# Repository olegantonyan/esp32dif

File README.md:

# esp32dif

Wi-Fi to S/PDIF receiver. The PC sends audio over Wi-Fi, and an ESP32-C5-DevKitC-1 plays it on a PiFi Digi+ (WM8804) S/PDIF board.

- Lossless 16/24-bit PCM, 32–192 kHz, bit-perfect when PipeWire does not change the audio.
- Web UI, telnet and USB shell for setup and diagnostics.
- Firmware updates over Wi-Fi (OTA) with automatic rollback.
- Status and track title on two small OLED screens.

Firmware: ESP-IDF 6.1. Technical details: [docs/internals.md](docs/internals.md). Digi+ bring-up notes: [docs/digi-bringup.md](docs/digi-bringup.md).

## Build and flash

```sh
make build
make flash-monitor   # first time, over USB; TTY_PORT=/dev/ttyACM0 by default
make ota             # later, over Wi-Fi; ESP_HOST=esp32dif.local, ESP_PASSWORD=esp32dif-admin by default
```

Use the board's **USB** port (`/dev/ttyACM0`), not **UART** (`/dev/ttyUSB0` has no console).

Build settings are in `sdkconfig.defaults`. To create `sdkconfig` again: `rm sdkconfig && idf.py set-target esp32c5`.

## First setup

1. Flash the board over USB.
2. With no saved Wi-Fi, the board starts its own Wi-Fi network (access point) `esp32dif`. The password is on the OLED (default `esp32dif-admin`).
3. Join it from a phone or PC and open `http://192.168.4.1`. Log in as `admin` with the same password.
4. Pick your Wi-Fi network and press **Connect**. The board saves it after it gets an IP address.
5. Open `http://esp32dif.local` from your home network. The board's access point turns off 2 minutes after the connection works.

On the USB shell you can do the same with `wifi connect <ssid> <password>`.

## Access and settings

One password protects the web UI, telnet, the board's access point and audio senders. The USB shell has no password.

| Way | How |
|---|---|
| Web UI | `http://esp32dif.local` (or `http://192.168.4.1` on the access point), user `admin`. Status (with the current player and track), Wi-Fi, hostname, password, firmware upload, reboot. |
| Telnet | `telnet esp32dif.local`. Same commands as USB, one session at a time, logout after 10 minutes without input. |
| USB | `make monitor` |

Change the hostname and password in the web UI, or with `config hostname <name>` and `config password <pw>`. The board saves them and uses them at once. The back OLED shows the current password (128x64 always, 128x32 while the access point runs without Wi-Fi; if it's asleep, press a remote key or reboot), and `config password` works over USB, so you can't lock yourself out.

The password travels as plain text over HTTP and telnet. This is fine on a home network, but not on networks you don't trust.

## Wi-Fi

- The board connects to the saved network at every boot. If the connection drops, it tries again: 3 times at once, then after 5, 10, 20 and 40 s, then every 60 s.
- Band `auto` (default) prefers 5 GHz. Use `wifi connect -b 5` or `-b 2.4` to force a band.
- Power save is off, for low latency.
- The board gets its IP address from DHCP and answers as `<hostname>.local` (mDNS).
- **Access point:** the board starts its own network (named after the hostname, WPA2, the device password, `192.168.4.1`) when no network is saved, after `wifi disconnect`, or after 60 s without an IP address. It turns off 2 minutes after the home connection works again.

## Firmware updates (OTA)

`make ota`, or upload `build/esp32dif.bin` in the web UI. The board has two firmware slots. A new firmware is confirmed 60 s after it starts. If the board resets before that, it starts the old firmware again. `ota status` shows both slots; `ota rollback` goes back to the old firmware.

The first flash with this partition layout must be over USB (`make flash`). The saved Wi-Fi is kept.

If you rename the project, flash over USB too: OTA accepts only firmware with the same project name.

## Playing audio from the PC

The PC runs the `esp32dif-sink` service. It adds an output device "S/PDIF over Wi-Fi" to PipeWire. Select it in the sound settings, or play a file with `pw-play --target=esp32dif-rtp file.wav`.

### Install

Install the `esp32dif-sink` package from [repositories.omnipackage.org/esp32dif](https://repositories.omnipackage.org/esp32dif/install.html) (openSUSE, Fedora, Debian, Ubuntu, Arch, Manjaro). It is built from every master push that changes the sink. Then start the service:

```sh
systemctl --user daemon-reload && systemctl --user enable --now esp32dif-sink
journalctl --user -u esp32dif-sink -f
```

To turn it off for your user: `systemctl --user mask esp32dif-sink`.

- **Password:** every 10 s the service logs in to the board with `SPDIF_PASSWORD` (default `esp32dif-admin`). The board plays audio only from computers that logged in during the last 60 s. With a wrong password, the service logs an error and doesn't create the device.
- **Board offline:** the device disappears about 30 s after the board stops answering, and comes back about 10 s after the board returns. If the board's IP address changes, the service follows it.
- **Remote buttons:** the service also connects to the board on TCP 5005 and turns IR remote buttons, the board's `player` command and the web UI's Player buttons into media player commands with `playerctl`: previous, play/pause, next. They go to the player you used last. Volume up/down and mute change the volume of this PC's `esp32dif-rtp` device with `pactl` (steps of `SPDIF_VOLUME_STEP` %, up to 100 %); the audio stays bit-perfect only at 100 %. With two PCs connected, only the one streaming to the board gets them. Known remotes: Edifier S2000MKII (`ir keys`). Turn it off with `SPDIF_REMOTE=0`.
- **Track title:** over the same connection the service sends the artist, title, name and playback status of that player when any of them changes. While this PC is the board's last RTP source and the service stays connected, the front OLED shows the artist, the title and a play/pause/stop icon with the player name and id in a double-height font; long ones scroll. Between them it shows the device volume (`vol 45%` or `vol muted`), however you change it. Latin, accented Latin and Cyrillic letters are shown; other characters show as `?`.
- **Firewall:** allow mDNS on the PC (`firewall-cmd --permanent --zone=public --add-service=mdns`, then `firewall-cmd --reload`). Without it, `esp32dif.local` doesn't work; use the IP address instead.

### Settings

Settings go in `~/.config/esp32dif-sink.conf`, for example:

```sh
SPDIF_HOST=esp32dif.local
SPDIF_RATE=44100
SPDIF_FORMAT=S24BE
SPDIF_PASSWORD=esp32dif-admin
```

Run `chmod 600` on this file, because it has the password. Apply changes with `systemctl --user restart esp32dif-sink`. When you change the board's hostname or password, change them here too.

Other settings: `SPDIF_PORT` (5004), `SPDIF_SAP_PORT` (9875), `SPDIF_CHECK_S` (10), `SPDIF_MISSES` (3), `SPDIF_REMOTE` (1), `SPDIF_REMOTE_PORT` (5005), `SPDIF_VOLUME_STEP` (5).

### Without the package

If there is no package for your distro, link the files from this folder. The script needs `bash`, `pipewire`, `curl`, `playerctl`, `pactl` (`pulseaudio-utils`, `libpulse` on Arch) and `nss-mdns`.

```sh
ln -s "$PWD/pipewire/esp32dif-sink" ~/.local/bin/esp32dif-sink
systemctl --user link "$PWD/pipewire/esp32dif-sink.service"
systemctl --user enable --now esp32dif-sink
```

Or run it in a terminal:

```sh
pipewire/esp32dif-sink                              # esp32dif.local, 48000 Hz, S24BE
pipewire/esp32dif-sink esp32dif.local 44100 S24BE   # host, rate, format
```

### Sound quality

For bit-perfect output:
- set the device volume to 100 %,
- play nothing else at the same time,
- use the same rate in the file, the sink and the PipeWire graph. The default PipeWire graph runs only at 48 kHz. Add `default.clock.allowed-rates = [ 44100 48000 ]` to allow 44.1 kHz too, then set `SPDIF_RATE=44100`.

Measured with `digi decode -d` (24-bit noise and −3 dBFS sines, compared with the file):

| Path | Result |
|---|---|
| 48 kHz file → 48 kHz sink, 100 % volume | bit-perfect (269/269 frames) |
| same at 90 % volume | 0 frames exact |
| 44.1 kHz file → 44.1 kHz graph and sink | bit-perfect (270/270 frames) |
| 44.1 kHz → 48 kHz (resampled), 997 Hz / 15 kHz | SINAD 138.1 / 138.8 dB, error −144 dBFS |
| 48 kHz → 44.1 kHz (resampled), 15 kHz | SINAD 139.6 dB |
| native, 997 Hz (24-bit limit) | SINAD 143 dB |

How it works:
- The board plays a stream only when it has a matching SAP announcement (L16 or L24 stereo). It switches the WM8804 to the announced rate.
- The buffer adds 250 ms of latency. Video players don't know about it, so video and sound can be out of sync. The buffer is in PSRAM (1152 KB, 4 s at 48 kHz 24-bit), or 64 KB of internal RAM without PSRAM.
- The board slowly adjusts its clock to the PC's clock, so the buffer never runs empty or full. This doesn't change the audio data.
- `rtp status` shows senders, format, lost packets, jitter, buffer level, underruns and clock adjustment.

## Wiring

### Pins

| Function | GPIO | Header |
|---|---|---|
| RGB LED (WS2812) | 27 | J3 pin 7 |
| OLED and Digi+ I2C SDA / SCL | 8 / 9 | J1 pin 9 / 10 |
| Digi+ I2S BCLK / WS / DOUT | 24 / 23 / 4 | J3 pin 4 / 5 / 8 |
| S/PDIF monitor (optional, for `digi spdif`) | 5 | J3 pin 9 |
| IR receiver output (Digi+ HAT or any 38 kHz receiver, 3.3 V) | 10 | J1 pin 11 |
| BOOT button | 28 | J3 pin 11 |
| USB D- / D+ | 13 / 14 | J3 pin 14 / 13 |
| UART0 TX / RX | 11 / 12 | J3 pin 2 / 3 |

Don't use for new wiring: strapping pins 2, 3, 7, 25, 26, 27, 28; flash/PSRAM pins 16–22 (and 15 on PSRAM modules); 0 and 1 if a 32 kHz crystal is fitted.

Pins and I2C addresses can be changed in `idf.py menuconfig` (Board OLED, Board I2C bus, Board Digi+, Board LED, Board IR receiver).

### OLED

Two SSD1306 I2C modules on the same bus: **back** 0.91" 128x32 at 0x3C (status), **front** 0.96" 128x64 at 0x3D (track). Both are wired in parallel to header **J1** (the header with `3V3` at pin 1, see the [DevKitC-1 user guide](https://docs.espressif.com/projects/esp-dev-kits/en/latest/esp32c5/esp32-c5-devkitc-1/user_guide.html)):

| OLED pin | DevKitC-1 pin | Label on board |
|---|---|---|
| GND | J1 pin 15 | `G` |
| VCC | J1 pin 1 | `3V3` |
| SCL | J1 pin 10 | `9` |
| SDA | J1 pin 9 | `8` |

- Use 3V3, not 5V. With 5V the module's pull-ups would pull SDA/SCL to 5 V.
- 0.91" 128x32 modules are fixed at 0x3C (the panel has no address pin). Most 0.96" 128x64 modules have an address resistor on the back; move it to get 0x3D. `i2cscan` shows which addresses answer.
- Addresses, heights and 180° rotation of both displays can be changed in menuconfig (Board OLED).
- The board also works with one display or none.

### Digi+ (WM8804 S/PDIF HAT)

PiFi Digi+ 1.0, a HiFiBerry Digi+ clone. HAT pins are the physical pins of its 40-pin Raspberry Pi header.

| HAT pin | DevKitC-1 pin | Label on board | Signal |
|---|---|---|---|
| 2 | J1 pin 14 | `5V` | 5 V (the HAT makes its own 3.3 V) |
| 6 | J1 pin 15 | `G` | ground |
| 3 | J1 pin 9 | `8` | I2C SDA, shared with the OLEDs |
| 5 | J1 pin 10 | `9` | I2C SCL, shared with the OLEDs |
| 12 | J3 pin 4 | `24` | I2S BCLK, HAT → ESP |
| 35 | J3 pin 5 | `23` | I2S WS (LRCLK), HAT → ESP |
| 40 | J3 pin 8 | `4` | I2S DOUT, ESP → HAT |
| 39 | J3 pin 1 | `G` | ground, next to the I2S wires |
| 22 | J3 pin 9 | `5` | S/PDIF monitor (optional, for `digi spdif`), HAT → ESP |

- **Add 2.2 kΩ pull-ups** from SDA and SCL to 3V3. Without them, I2C fails while audio plays.
- Leave HAT pin 1 (3V3) open: the HAT makes its own 3.3 V from 5V.
- HAT pin 22 (BCM GPIO25) is unused by the HAT. For the S/PDIF monitor, solder a wire on the HAT from the optical transmitter's data pin to pin 22. Don't add a series resistor: the HAT's 200 Ω before the transmitter already protects TX0, and an extra 1 kΩ caused decode errors.
- Run `digi probe` to check the wiring step by step. More notes: [docs/internals.md](docs/internals.md#digi-wiring-notes).

## OLED screens

Back:

```
48kHz 24-bit         format
rtp 102ms buf        source: rtp, tone, idle; noI2C = no I2C to the WM8804
192.168.0.21         IP address or Wi-Fi state; on 128x32 the password while the access point is on without Wi-Fi
AP:- up 0d 01:02:03  access point clients (- = off), uptime
esp32dif.local       128x64 only: hostname
pw esp32dif-admin    128x64 only: password (first 18 characters)
heap 312 KB free     128x64 only: free memory
```

Front, while a PC sends the track title (see [Install](#install)), otherwise `no track`. Double-height font, 10 characters per line; longer text scrolls:

```
Pink Floyd           artist
Shine On Y           title
                     
▶ mpz (org           playback status icon, player and id
```

To prevent burn-in, each screen turns off after 2 minutes without activity. A remote key, a format or source change, a Wi-Fi or access point change, or any `oled` command wakes it. Change the timeout with `oled idle` or in menuconfig (Board OLED).

## Shell commands

The same commands work on USB and telnet. Line editing, history, Tab completion and `help [cmd]` are available.

| Command | What it does |
|---|---|
| `config show [-p]` | hostname, password (hidden without `-p`), access point |
| `config hostname <name>` | set hostname: a-z, 0-9, `-`, up to 32 characters |
| `config password <pw>` | set password: 8–63 characters |
| `wifi scan` | list nearby networks |
| `wifi connect [ssid] [password] [-b 2.4\|5\|auto] [-n] [-t s]` | join a network; it is saved after it gets an IP (`-n`: don't save). Without ssid: the saved network |
| `wifi status` | connection, signal, IP address, access point |
| `wifi saved [-p]` / `forget` / `disconnect` | show / delete the saved network / disconnect |
| `rtp status` / `rtp reset` | audio receiver statistics / reset them |
| `ota status` / `ota rollback` | firmware slots / go back to the old firmware |
| `digi status` | WM8804 found, crystal, rate, pins, tone |
| `digi probe` | check the Digi+ wiring step by step |
| `digi rate <hz>` | 32000, 44100 (default), 48000, 88200, 96000, 176400, 192000 |
| `digi tone <hz> [-l 0-100]` / `digi stop` | play a test sine (level in %, default 10) / stop it |
| `digi reg <reg> [value]` | read or write a WM8804 register |
| `digi spdif` | check the S/PDIF output on the monitor pin |
| `digi decode [-d]` | decode any S/PDIF signal on the monitor pin (`-d`: print all frames) |
| `digi trim <ppm>` / `digi trimtest <ppm>` | adjust the WM8804 clock / test clock adjustment |
| `ir status` / `ir keys` | IR line level, last frame and connected PCs / known remote buttons |
| `player prev\|play\|next` / `vol+\|vol-\|mute` / `status` | control the PC media player / PC device volume / connected PCs, track and volume |
| `ir watch [-r]` | print remote codes live (`-r`: pulse widths); add new buttons to `components/remote/keymap.c` |
| `oled [back\|front] status` / `on` / `off` / `contrast <0-255>` / `idle <s>` | display state / power / contrast / turn off after s idle seconds (0 = never); both displays unless one is named |
| `oled [back\|front] print <row> <text>` / `clear` / `auto` | write text / clear / back to the status screen |
| `led color <color>` | color: name, `#rrggbb` or `r,g,b` (`led presets` lists names) |
| `led blink\|breathe <color> [-p ms]` / `led rainbow [-p ms]` | effects |
| `led off` / `led auto` / `led brightness <0-100>` / `led status` | LED control (off by default) |
| `sysinfo` / `version` / `uptime` | chip, firmware and uptime information |
| `free [-h]` / `ps` | memory / tasks |
| `i2cscan` | addresses that answer on the I2C bus |
| `reboot [-d ms]` | restart |

LED and OLED changes made with commands are not saved; they reset at reboot.

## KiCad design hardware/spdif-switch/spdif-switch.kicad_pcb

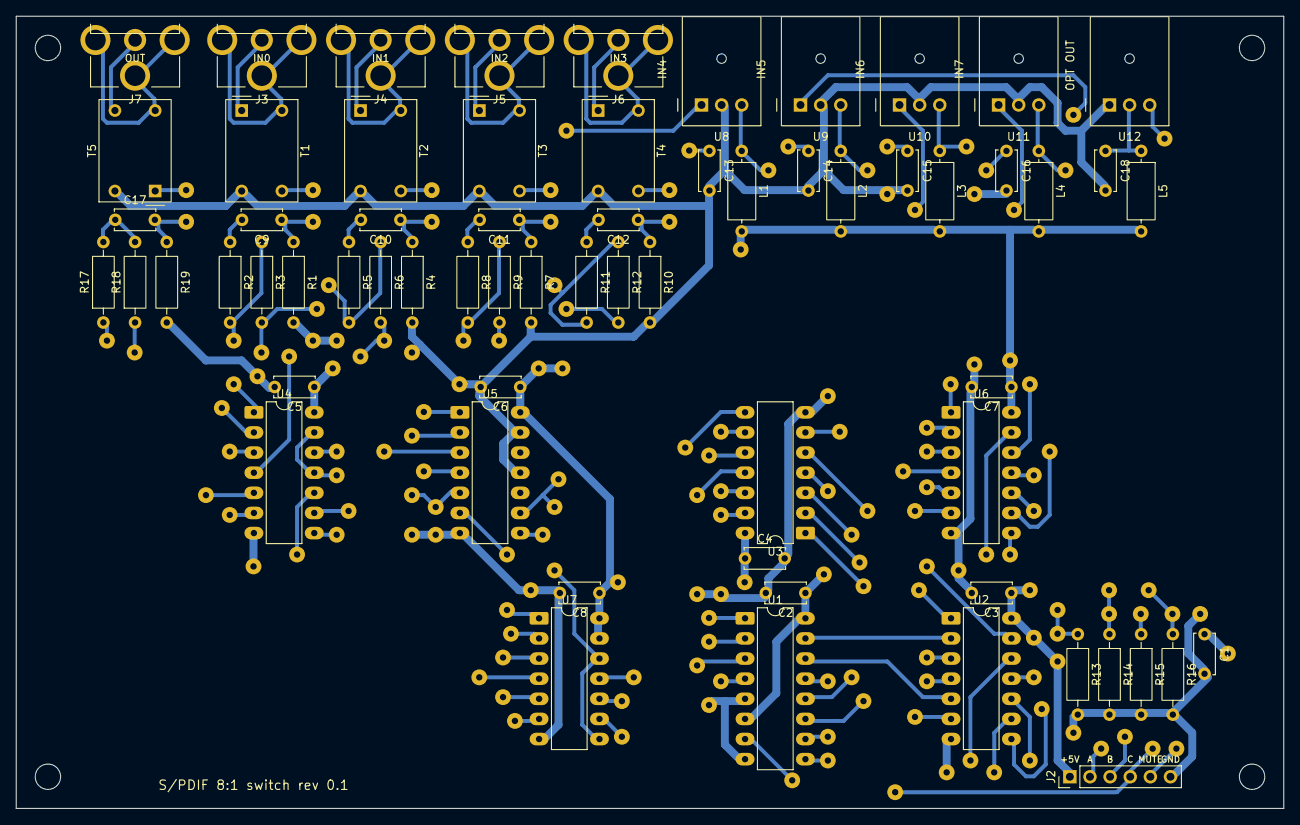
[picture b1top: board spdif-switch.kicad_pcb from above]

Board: 2 copper layers, 160.0 x 100.0 mm, 146 parts (0 on the bottom side), 73 nets.

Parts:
C1: 10u; C_Disc_D5.0mm_W2.5mm_P5.00mm
C2, C3, C4, C5, C6, C7, C8, C9, C10, C11, C12, C13, C14, C15, C16, C17, C18: 100n; C_Disc_D5.0mm_W2.5mm_P5.00mm
H1, H2, H3, H4: M3; MountingHole_3.2mm_M3
J2: PWR+CTRL; PinHeader_1x06_P2.54mm_Vertical
J3, J4, J5, J6, J7: RCA; RCA_Jack_RightAngle_RCJ-01
L1, L2, L3, L4, L5: 47u; L_Axial_L7.0mm_D3.3mm_P10.16mm_Horizontal_Fastron_MICC
R1, R4, R7, R10: 75; R_Axial_DIN0207_L6.3mm_D2.5mm_P10.16mm_Horizontal
R2, R5, R8, R11: 1k; R_Axial_DIN0207_L6.3mm_D2.5mm_P10.16mm_Horizontal
R3, R6, R9, R12, R13, R14, R15, R16: 10k; R_Axial_DIN0207_L6.3mm_D2.5mm_P10.16mm_Horizontal
R17, R18: 750; R_Axial_DIN0207_L6.3mm_D2.5mm_P10.16mm_Horizontal
R19: 91; R_Axial_DIN0207_L6.3mm_D2.5mm_P10.16mm_Horizontal
T1, T2, T3, T4, T5: PE-65612; Transformer_Pulse_PE-65612
U1: 74HC138; DIP-16_W7.62mm_LongPads
U2, U6: 74HC32; DIP-14_W7.62mm_LongPads
U3, U7: 74HC08; DIP-14_W7.62mm_LongPads
U4: 74HC04; DIP-14_W7.62mm_LongPads
U5: 74HC14; DIP-14_W7.62mm_LongPads
U8, U9, U10, U11: DLR1150; DLR1150_DLT1150
U12: DLT1150; DLR1150_DLT1150
W1, W2, W3, W4, W5: wire 4mm
W6, W18: wire 12mm
W7: wire 10mm
W8: wire 13mm
W9, W51, W66: wire 16mm
W10, W19, W21, W52: wire 26mm
W11: wire 31mm
W12: wire 6mm
W13, W38, W73: wire 40mm
W14: wire 54mm
W15: wire 78mm
W16, W32: wire 98mm
W17, W35: wire 41mm
W20, W53, W56: wire 38mm
W22: wire 51mm
W23: wire 44mm
W24: wire 46mm
W25: wire 66mm
W26: wire 55mm
W27: wire 60mm
W28: wire 70mm
W29: wire 20mm
W30, W61: wire 97mm
W31, W77: wire 39mm
W33: wire 68mm
W34, W54, W70, W76: wire 36mm
W36: wire 80mm
W37, W43: wire 58mm
W39: wire 100mm
W40: wire 171mm
W41: wire 29mm
W42: wire 99mm
W44, W69: wire 24mm
W45: wire 48mm
W46: wire 134mm
W47, W67: wire 17mm
W48, W65: wire 14mm
W49: wire 9mm
W50: wire 90mm
W55, W64, W68: wire 22mm
W57: wire 23mm
W58: wire 86mm
W59: wire 45mm
W60: wire 103mm
W62: wire 15mm
W63, W74: wire 30mm
W71: wire 21mm
W72: wire 42mm
W75: wire 73mm

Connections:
+5V: C1.1, C2.1, C3.1, C4.1, C5.1, C6.1, C7.1, C8.1, J2.1, L1.2, L2.2, L3.2, L4.2, L5.2, U1.6, U1.16, U2.14, U3.14, U4.14, U5.14, U6.14, U7.13, U7.14, W51.1, W52.1, W53.1, W54.1, W55.1, W56.1
/IN0: U2.1, U5.2, W39.1
/IN1: U2.4, U5.4, W46.1
/IN2: U2.9, U5.6, W61.1
/IN3: U2.12, U5.8, W50.1
/IN4: U6.1, U8.1, W36.1
/IN5: U6.4, U9.1, W33.1
/IN6: U6.9, U10.1, W45.1
/IN7: U6.12, U11.1, W44.1
/MUTE: J2.5, R16.1, U1.4, W41.1, W42.1
/MUX: U4.11, U4.13, U7.8, U7.12, W38.1
/SEL_A: J2.2, R13.1, U1.1, W29.1, W30.1
/SEL_B: J2.3, R14.1, U1.2, W31.1, W32.1
/SEL_C: J2.4, R15.1, U1.3, W34.1, W35.1
/~SEL0: U1.15, U2.2
/~SEL1: U1.14, U2.5
/~SEL2: U1.13, U2.10, W72.1
/~SEL3: U1.12, U2.13, W57.1
/~SEL4: U1.11, U6.2, W24.1
/~SEL5: U1.10, U6.5, W23.1
/~SEL6: U1.9, U6.10, W27.1
/~SEL7: U1.7, U6.13, W43.1
GND: C1.2, C2.2, C3.2, C4.2, C5.2, C6.2, C7.2, C8.2, C13.2, C14.2, C15.2, C16.2, C18.2, J2.6, R1.2, R4.2, R7.2, R10.2, R13.2, R14.2, R15.2, R16.2, R19.2, T1.3, T2.3, T3.3, T4.3, T5.2, U1.5, U1.8, U2.7, U3.7, U4.7, U5.7, U5.11, U5.13, U6.7, U7.7, U8.2, U9.2, U10.2, U11.2, U12.1, W62.1, W63.1, W64.1, W65.1, W66.1, W67.1, W68.1, W69.1, W70.1, W71.1
unnamed: C9.2, R2.1
unnamed: C10.2, R5.1
unnamed: C11.2, R8.1
unnamed: C12.2, R11.1
unnamed: C17.1, R17.2, R18.2
unnamed: J3.2, T1.2
unnamed: J3.1, T1.1
unnamed: J4.2, T2.2
unnamed: J4.1, T2.1
unnamed: J5.2, T3.2
unnamed: J5.1, T3.1
unnamed: J6.2, T4.2
unnamed: J6.1, T4.1
unnamed: J7.2, T5.3
unnamed: J7.1, T5.4
unnamed: R2.2, R3.1, U4.1, W12.1
unnamed: R3.2, U4.2, U5.1, W18.1, W19.1
unnamed: R5.2, R6.1, U4.3, W20.1
unnamed: R6.2, U4.4, U5.3, W48.1, W49.1
unnamed: R8.2, R9.1, U4.5, W28.1
unnamed: R9.2, U4.6, U5.5, W73.1, W74.1
unnamed: R11.2, R12.1, U4.9, W37.1
unnamed: R12.2, U4.8, U5.9, W76.1, W77.1
unnamed: R17.1, U4.10, W22.1
unnamed: R18.1, U4.12, W17.1
unnamed: C9.1, R1.1, T1.4, W3.1
unnamed: C10.1, R4.1, T2.4, W2.1
unnamed: C11.1, R7.1, T3.4, W5.1
unnamed: C12.1, R10.1, T4.4, W4.1
unnamed: C17.2, R19.1, T5.1, W1.1
unnamed: U2.3, U3.1, W47.1
unnamed: U2.6, U3.2, W21.1
unnamed: U2.8, U3.4, W75.1
unnamed: U2.11, U3.5, W59.1
unnamed: U3.3, U7.1, W60.1
unnamed: U3.6, U7.2, W58.1
unnamed: U3.8, U7.4, W26.1
unnamed: U3.9, U6.3, W13.1
unnamed: U3.10, U6.6, W14.1
unnamed: U3.11, U7.5, W25.1
unnamed: U3.12, U6.8, W15.1
unnamed: U3.13, U6.11, W16.1
unnamed: U7.3, U7.9, W11.1
unnamed: U7.6, U7.10, W10.1
unnamed: C13.1, L1.1, U8.3, W6.1
unnamed: C14.1, L2.1, U9.3, W8.1
unnamed: C15.1, L3.1, U10.3, W9.1
unnamed: C16.1, L4.1, U11.3, W7.1
unnamed: U7.11, U12.3, W40.1
unnamed: C18.1, L5.1, U12.2
